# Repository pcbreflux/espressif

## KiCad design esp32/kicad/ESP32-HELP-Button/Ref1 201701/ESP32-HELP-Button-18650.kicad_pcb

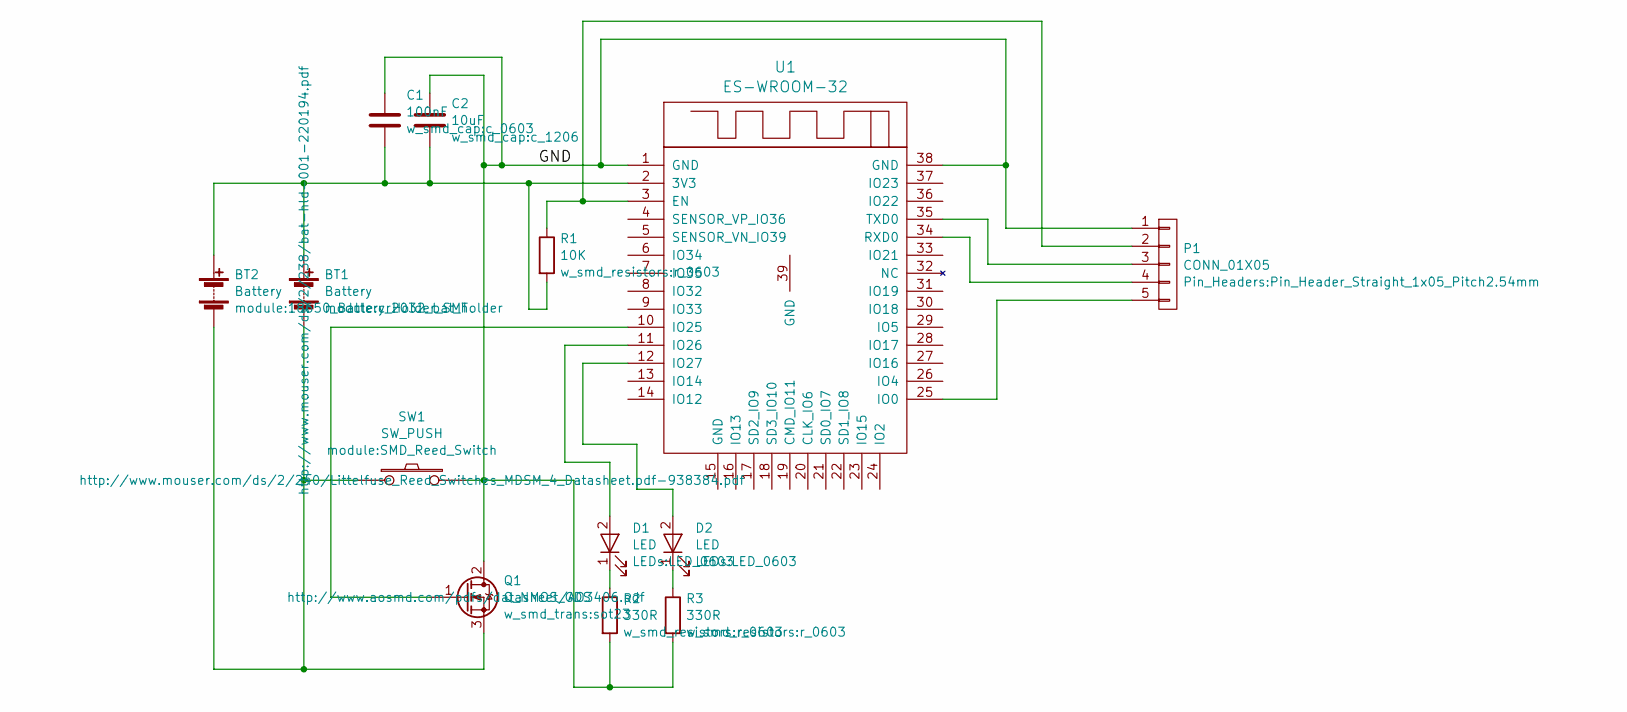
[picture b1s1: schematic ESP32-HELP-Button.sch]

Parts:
BT1: Battery; cr2032_bat_holder; MFG Part Num BAT-HLD-001
BT2: Battery; 18650_Battery_Holder_SMT; MFG Part Num 1042P
C1: 100nF; c_0603; MFG Part Num 100nF 0603 capacitor X7R
C2: 10uF; c_1206; MFG Part Num 10uF 1206 capacitor X7R
D1: LED; LED_0603; MFG Part Num led green 0603
D2: LED; LED_0603; MFG Part Num led red 0603
P1: CONN_01X05; Pin_Header_Straight_1x05_Pitch2.54mm; MFG Part Num 22-28-4012
Q1: Q_NMOS_GDS; sot23; MFG Part Num AO3406
R1: 10K; r_0603; MFG Part Num 10k 0603 resistor 10%
R2, R3: 330R; r_0603; MFG Part Num 330R 0603 resistor 10%
SW1: SW_PUSH; SMD_Reed_Switch; MFG Part Num MDSM-4R-7-13
U1: ES-WROOM-32; ESP-WROOM-32-short; MFG Part Num esp-wroom-32

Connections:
/GND: C1.1, C2.1, P1.1, Q1.2 (D), R2.2, R3.2, SW1.2, U1.1 (GND), U1.38 (GND)
unnamed: BT1.1 (+), BT2.1 (+), C1.2, C2.2, R1.2, U1.2 (3V3)
unnamed: BT1.2 (-), BT2.2 (-), Q1.3 (S), SW1.1
unnamed: D1.1 (K), R2.1
unnamed: D1.2 (A), U1.11 (IO26)
unnamed: D2.1 (K), R3.1
unnamed: D2.2 (A), U1.12 (IO27)
unnamed: P1.2, R1.1, U1.3 (EN)
unnamed: P1.3, U1.35 (TXD0)
unnamed: P1.4, U1.34 (RXD0)
unnamed: P1.5, U1.25 (IO0)
unnamed: Q1.1 (G), U1.10 (IO25)

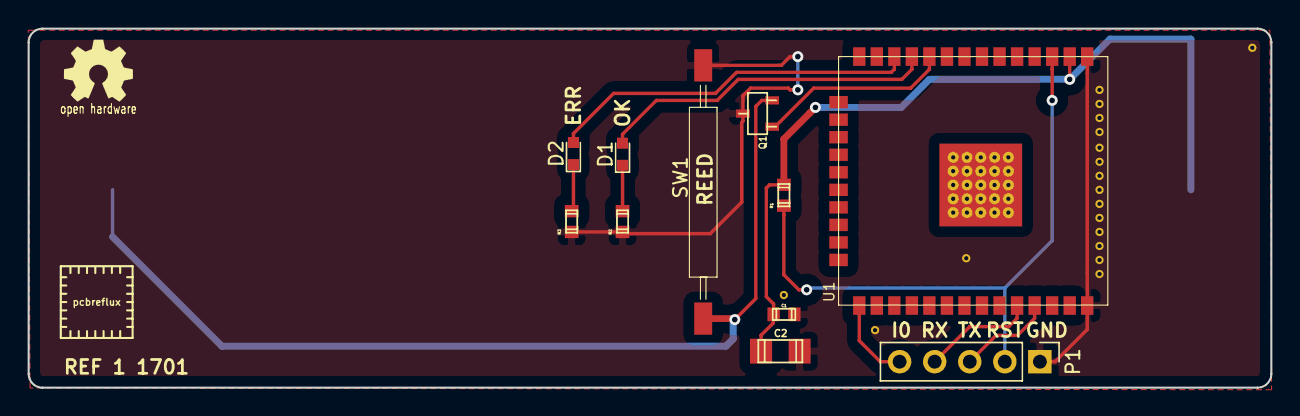
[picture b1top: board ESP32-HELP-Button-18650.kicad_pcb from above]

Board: 2 copper layers, 90.0 x 26.0 mm, 12 parts (1 on the bottom side), 12 nets.

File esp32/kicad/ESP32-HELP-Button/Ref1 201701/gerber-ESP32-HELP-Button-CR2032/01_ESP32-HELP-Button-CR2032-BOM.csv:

Reference, Value, Footprint, Datasheet, MFG Name, MFG Part Num, 1st Distrib PN, 1st Distrib Link, 2nd Distrib PN, 2nd Distrib Link,,Val,Package,PosX,PosY,Rot,Side
U1,ES-WROOM-32,module:ESP-WROOM-32-short,http://espressif.com/sites/default/files/documentation/esp_w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,espressif,esp-wroom-32,ESP-32S,http://www.analoglamb.com/product/esp3212-wifi-bluetooth-com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,ESP-32S-ALB,http://www.analoglamb.com/product/esp-32s-alb/,,-,,,,,
P1,CONN_01X05,Pin_Headers:Pin_Header_Straight_1x05_Pitch2.54mm,http://www.molex.com/webdocs/datasheets/pdf/en-us//002228505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,Molex,22-28-4012,pin header 40 pin male 2.54mm,https://www.aliexpress.com/wholesale?SearchText=pin+header+4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,538-22-28-5051,http://www.mouser.de/ProductDetail/Molex/22-28-5051/?qs=sGAE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,,-,,,,,
BT1,Battery,module:cr2032_bat_holder,http://www.mouser.com/ds/2/238/bat-hld-001-220194.pdf,Linx Technologies,BAT-HLD-001,712-BAT-HLD-001,http://www.mouser.de/ProductDetail/Linx-Technologies/BAT-HLD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,BAT-HLD-001-THM-ND,http://www.digikey.com/product-detail/en/linx-technologies-i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,,Battery,cr2032_bat_holder,95.067961,-58.473131,0.000000,bottom
Q1,Q_NMOS_GDS,w_smd_trans:sot23,http://www.aosmd.com/pdfs/datasheet/AO3406.pdf,Alpha & Omega Semiconductor Inc.,AO3406,ao3406 100pcs,https://www.aliexpress.com/wholesale?SearchText=ao3406+100pcs,785-1005-1-ND,http://www.digikey.com/product-detail/en/alpha-omega-semicon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,,Q_NMOS_GDS,sot23,97.790000,-53.149500,90.000000,top
SW1,SW_PUSH,module:SMD_Reed_Switch,http://www.mouser.com/ds/2/240/Littelfuse_Reed_Switches_MDSM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,Hamlin / Littelfuse,MDSM-4R-7-13,934-MDSM-4R-7-13,http://www.mouser.de/ProductDetail/Hamlin-Littelfuse/MDSM-4R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,F7839CT-ND,http://www.digikey.com/product-detail/en/littelfuse-inc/MDSM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,,SW_PUSH,SMD_Reed_Switch,93.853000,-67.997000,90.000000,top
R1,10K,w_smd_resistors:r_0603,,arbitrary,10k 0603 resistor 10%,10k 0603 resistor 1% 1000pcs,https://www.aliexpress.com/wholesale?SearchText=10k+0603+res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,603-RC0603JR-0710KL,http://www.mouser.de/ProductDetail/Yageo/RC0603JR-0710KL/?qs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,,10K,r_0603,99.695000,-59.065160,270.000000,top
R2,330R,w_smd_resistors:r_0603,,arbitrary,330R 0603 resistor 10%,330R 0603 resistor 10% 1000pcs,https://www.aliexpress.com/wholesale?SearchText=330R+0603+re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,603-RC0603JR-07330RL,http://www.mouser.de/ProductDetail/Yageo/RC0603JR-07330RL/?q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,,330R,r_0603,88.011000,-60.970160,90.000000,top
D1,LED,LEDs:LED_0603,,arbitrary,led green 0603,led green 0603 100pcs,https://www.aliexpress.com/wholesale?SearchText=led+green+06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,859-LTST-C190GKT,http://www.mouser.de/ProductDetail/Lite-On/LTST-C190GKT/?qs=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,,LED,LED_0603,88.011000,-56.096000,90.000000,top
D2,LED,LEDs:LED_0603,,arbitrary,led red 0603,led red 0603 100pcs,https://www.aliexpress.com/wholesale?SearchText=led+red+0603+100pcs,859-LTST-C190KRKT,http://www.mouser.de/ProductDetail/Lite-On/LTST-C190KRKT/?qs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,,LED,LED_0603,84.455000,-56.045000,90.000000,top
C2,10uF,w_smd_cap:c_1206,,arbitrary,10uF 1206 capacitor X7R,10uF 1206 capacitor X7R 100pcs,https://www.aliexpress.com/wholesale?SearchText=10uF+1206+ca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,581-1206ZC106KAT2A,http://www.mouser.de/ProductDetail/AVX/1206ZC106KAT2A/?qs=sG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,,10uF,c_1206,99.441000,-70.358000,0.000000,top
C1,100nF,w_smd_cap:c_0603,,arbitrary,100nF 0603 capacitor X7R,100nF 0603 capacitor X7R 1000pcs,https://www.aliexpress.com/wholesale?SearchText=100nF+0603+c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,710-885012206020,http://www.mouser.de/ProductDetail/Wurth-Electronics/8850122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,,100nF,c_0603,99.705160,-67.691000,0.000000,top
BT2,Battery,module:18650_Battery_Holder_SMT,http://www.mouser.com/ds/2/215/042P-744096.pdf,Keystone Electronics,1042P,18650 Battery Holder Battery Storage Box With Bronze PinsTBH-18650-1C-SMT,https://www.aliexpress.com/item/5Pcs-lot-18650-Battery-Holde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,534-1042P,http://www.mouser.de/ProductDetail/Keystone-Electronics/1042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,,-,,,,,
R3,330R,w_smd_resistors:r_0603,,arbitrary,330R 0603 resistor 10%,330R 0603 resistor 10% 1000pcs,https://www.aliexpress.com/wholesale?SearchText=330R+0603+re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,603-RC0603JR-07330RL,http://www.mouser.de/ProductDetail/Yageo/RC0603JR-07330RL/?q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,,330R,r_0603,84.328000,-60.970160,90.000000,top
